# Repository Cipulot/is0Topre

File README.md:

# is0Topre

## Introduction

Topre version of the iconic is0 board.

This project is a continuation of my development of open source EC boards.

Below is the KLE of the supported layout:

## Technical information

- Layout size: ISO enter
- Compatible switches: EC switches (Topre and NIZ)
- Microcontroller: Atmega32u4
- Connector: USB Type C
- Firmware compatibility: QMK (with VIA/VIAL support)
- Protection hardware:
  - Fused
  - ESD protection

**Addition: an empty spot for a 3.5x3.5mm SK series LED has been added to the back of the PCB, in case you want to manually add a bit of lighting.

## Renders and Prototypes

### is0Topre PCB

#### Render

### Plate

#### Render

Topre housing compatible plate:

MX plate mounted stabilizer compatible plate:

#### Prototype

## WIP

Atmel MCU based firmware is validated, you can find the precompiled `.hex` (Vial compatible) and `.json` file for VIA in the firmware folder.

STM32 based MCU version is in development.

## Compatibility with is0 case

Given the difference in height and mounting system some modifications are needed.

At the time of ordering the PCBs be sure to use the following specs:

- 1.2mm thickness for the main PCB
- 0.6mm for the plates

In order to have the correct fit place in the marked spots adhesive tape, specifically:

- 2pcs, 0.4mm thick on the main PCB
- 4pcs, 0.1mm thick on the plates

These will ensure that all the tollerances are met and a secure fit is achieved.

## License

<br />This work is licensed under a <a rel="license" href="http://creativecommons.org/licenses/by-nc-sa/4.0/">Creative Commons Attribution-NonCommercial-ShareAlike 4.0 International License</a>.

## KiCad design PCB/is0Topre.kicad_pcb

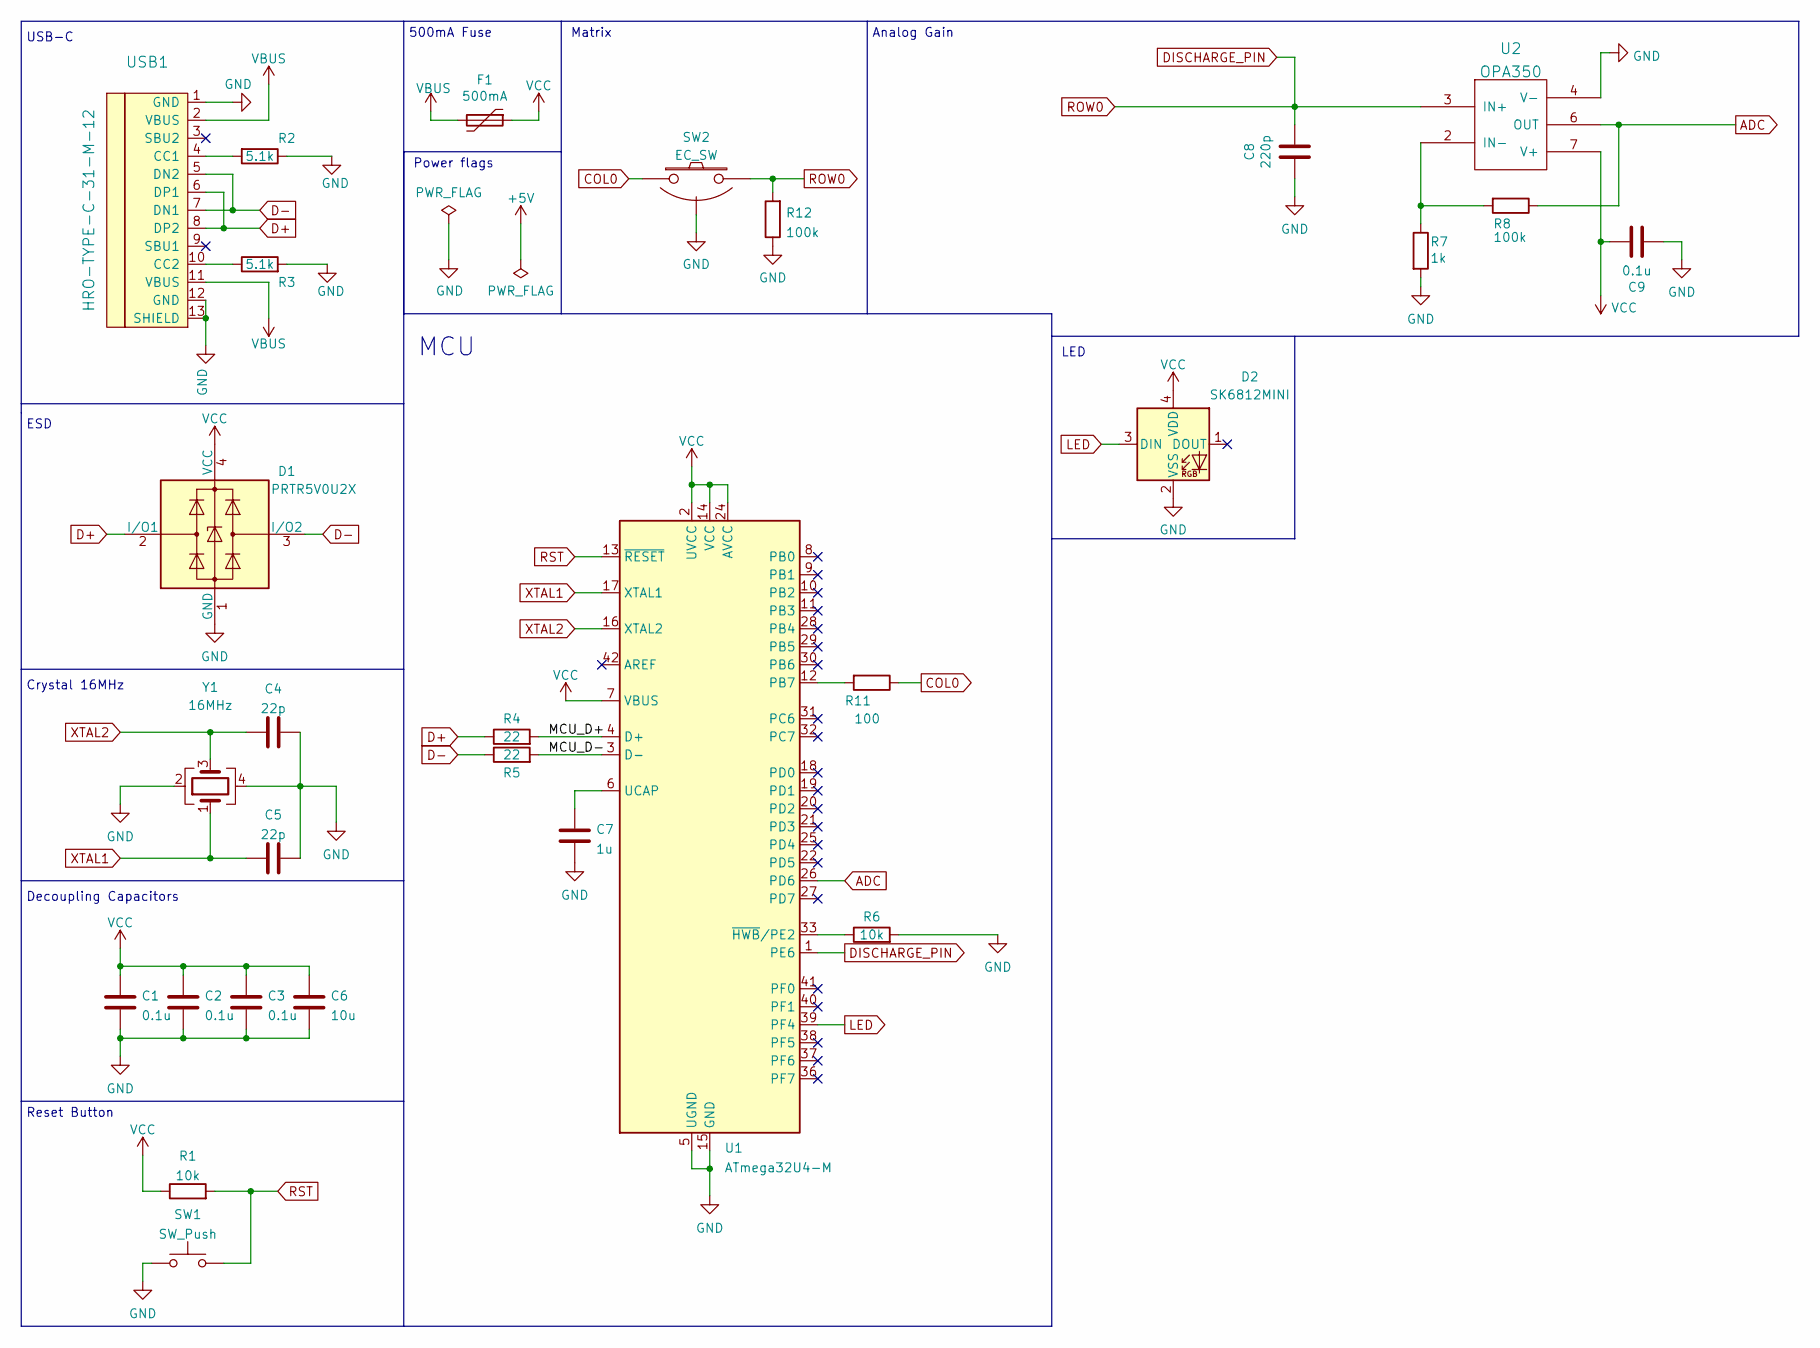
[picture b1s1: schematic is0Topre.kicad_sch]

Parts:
C1, C2, C3, C9: 0.1u; C_0603_1608Metric
C4, C5: 22p; C_0603_1608Metric
C6: 10u; C_0603_1608Metric
C7: 1u; C_0603_1608Metric
C8: 220p; C_0603_1608Metric
D1: PRTR5V0U2X; SOT-143
D2: SK6812MINI; LED_SK6812MINI_PLCC4_3.5x3.5mm_P1.75mm
F1: 500mA; Fuse_1206_3216Metric; LCSC Part # C70076
R1, R6: 10k; R_0603_1608Metric
R2, R3: 5.1k; R_0603_1608Metric
R4, R5: 22; R_0603_1608Metric
R7: 1k; R_0603_1608Metric
R8, R12: 100k; R_0603_1608Metric
R11: 100; R_0603_1608Metric
SW1: SW_Push; Jumper-UserFriendly-Small
SW2: EC_SW; ecs_pad_2U_no_ring
U1: ATmega32U4-M; QFN-44-1EP_7x7mm_P0.5mm_EP5.2x5.2mm; LCSC Part # C112161
U2: OPA350; SOIC-8_3.9x4.9mm_P1.27mm
USB1: HRO-TYPE-C-31-M-12; HRO-TYPE-C-31-M-12-Assembly
Y1: 16MHz; Crystal_SMD_3225-4pin_3.2x2.5mm; LCSC Part # C13738

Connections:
/MCU_D+: R4.2, U1.4 (D+)
/MCU_D-: R5.2, U1.3 (D-)
ADC: R8.1, U1.26 (PD6), U2.6 (OUT)
COL0: R11.1, SW2.1
D+: D1.2 (I/O1), R4.1, USB1.6 (DP1), USB1.8 (DP2)
D-: D1.3 (I/O2), R5.1, USB1.5 (DN2), USB1.7 (DN1)
DISCHARGE_PIN: C8.1, R12.2, SW2.2, U1.1 (PE6), U2.3 (IN+)
GND: C1.2, C2.2, C3.2, C4.1, C5.1, C6.2, C7.2, C8.2, C9.1, D1.1 (GND), D2.2 (VSS), R2.1, R3.2, R6.2, R7.2, R12.1, SW1.1, SW2.3 (SG), U1.5 (UGND), U1.15 (GND), U1.23 (GND), U1.35 (GND), U1.43 (GND), U1.45 (GND), U2.4 (V-), USB1.1 (GND), USB1.12 (GND), USB1.13 (SHIELD), Y1.2, Y1.4
LED: D2.3 (DIN), U1.39 (PF4)
unnamed: C7.1, U1.6 (UCAP)
unnamed: R2.2, USB1.4 (CC1)
unnamed: R3.1, USB1.10 (CC2)
unnamed: R6.1, U1.33 (~HWB/PE2)
unnamed: R7.1, R8.2, U2.2 (IN-)
unnamed: R11.2, U1.12 (PB7)
RST: R1.2, SW1.2, U1.13 (~RESET)
VBUS: F1.2, USB1.2 (VBUS), USB1.11 (VBUS)
VCC: C1.1, C2.1, C3.1, C6.1, C9.2, D1.4 (VCC), D2.4 (VDD), F1.1, R1.1, U1.2 (UVCC), U1.7 (VBUS), U1.14 (VCC), U1.24 (AVCC), U1.34 (VCC), U1.44 (AVCC), U2.7 (V+)
XTAL1: C5.2, U1.17 (XTAL1), Y1.1
XTAL2: C4.2, U1.16 (XTAL2), Y1.3

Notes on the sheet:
USB-C
Analog Gain
LED
500mA Fuse
MCU
Decoupling Capacitors
Power flags
Matrix
Crystal 16MHz
ESD
Reset Button

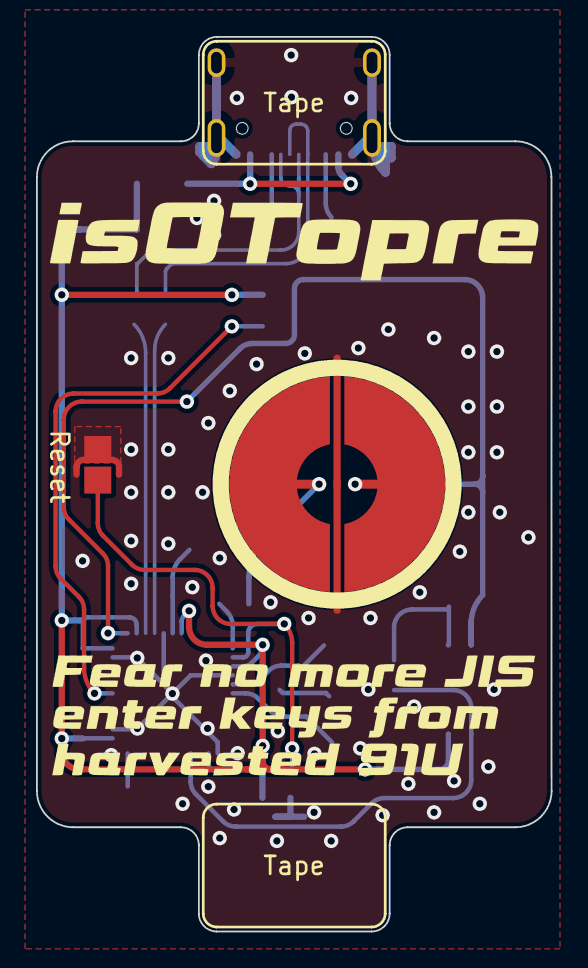
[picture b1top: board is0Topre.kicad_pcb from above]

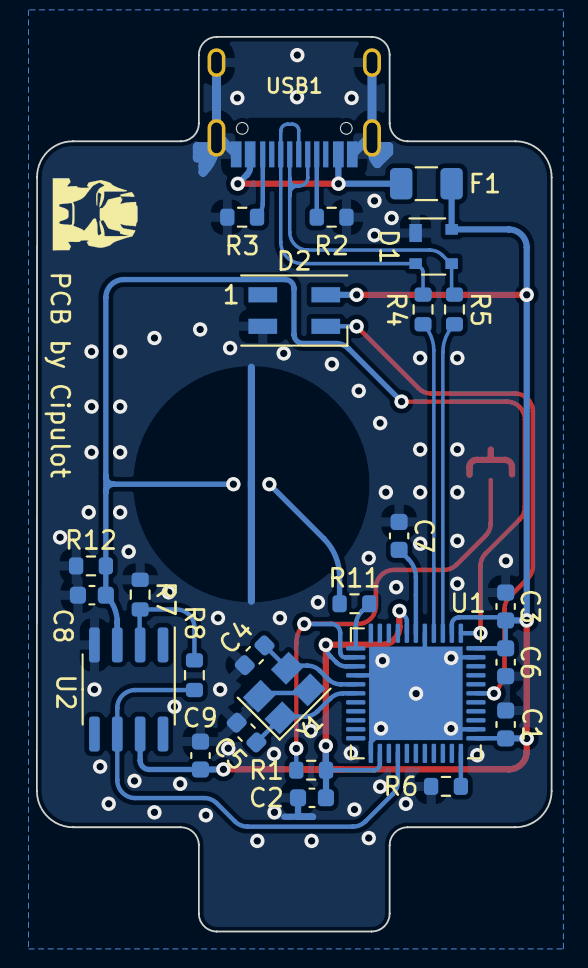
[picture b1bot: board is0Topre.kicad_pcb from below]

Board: 2 copper layers, 28.6 x 49.7 mm, 28 parts (26 on the bottom side), 20 nets.

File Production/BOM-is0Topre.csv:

Comment,Designator,Footprint,LCSC
HRO-TYPE-C-31-M-12,USB1,HRO-TYPE-C-31-M-12-Assembly,C165948
1u,C7,C_0603_1608Metric,C15849
PRTR5V0U2X,D1,SOT-143,C2827688
220p,C8,C_0603_1608Metric,C1603
100k,"R8,R12",R_0603_1608Metric,C25803
10k,"R6,R1",R_0603_1608Metric,C25804
10u,C6,C_0603_1608Metric,C96446
0.1u,"C1,C9,C3,C2",C_0603_1608Metric,C14663
22p,"C5,C4",C_0603_1608Metric,C1653
16MHz,Y1,Crystal_SMD_3225-4pin_3.2x2.5mm,C13738
5.1k,"R2,R3",R_0603_1608Metric,C23186
22,"R5,R4",R_0603_1608Metric,C23345
1k,R7,R_0603_1608Metric,C21190
500mA,F1,Fuse_1206_3216Metric,C70076
OPA350,U2,SOIC-8_3.9x4.9mm_P1.27mm,C13388
ATmega32U4-M,U1,QFN-44-1EP_7x7mm_P0.5mm_EP5.2x5.2mm,C112161
100,R11,R_0603_1608Metric,C22775

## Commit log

2022-06-03 Assets init
2022-06-03 PCB project init
2022-06-03 First production files
2022-06-03 Update images
2022-06-04 Added plate files
    Files for Topre 2u sw and MX compatible stabs through plate mounted stabilizer.
2022-06-04 Repo cleanup and additions
2022-06-04 Upload KLE and update README
2022-06-06 Fix for resistor missing
2022-06-06 Updated render
    Render picture updated after change in PCB to fix resistor error.
2022-06-14 Update of circuit after PCB testing
2022-06-14 Firmware upload
    Firmware upload after testing with hardware.
2022-06-14 Uploaded bottom view render picture
2022-06-14 Update firmware and PCB files for LED support
2022-06-16 Updated pic and production to add logo
2022-06-20 Update to add tape silkscreen
2022-06-30 Update of BOM
2022-07-25 Update BOM-is0Topre.csv
    Change to 8MHz resonator
2022-07-25 Update POS-is0Topre.csv
    Change label to 8MHz
2022-07-26 Align to new USB defs file in info.json
2022-07-26 Revert "Update BOM-is0Topre.csv"
    This reverts commit b2ed54e3cb7e963670c5bac463af23f9a7a3efb1.
2022-07-26 Revert "Update POS-is0Topre.csv"
    This reverts commit f306154f2dc278414dedb12f148aa883d78f8acf.
2022-08-16 Update BOM-is0Topre.csv
    Moved from MUR to MU bc usually cheaper option at JLC.
2022-08-22 Update firmware values
2022-08-23 Pic upload and readme update
2023-01-08 Update for 3d models
2023-03-26 Update README.md
    fixed plate picture link
2023-11-15 Update LICENSE
    Change of License
2024-03-03 Updated the License for the project and relative details.
2024-06-08 is0Topre update
